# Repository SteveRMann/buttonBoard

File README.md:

# buttonBoard
Test board with four buttons, two LEDs and one PWM driver (200mA).

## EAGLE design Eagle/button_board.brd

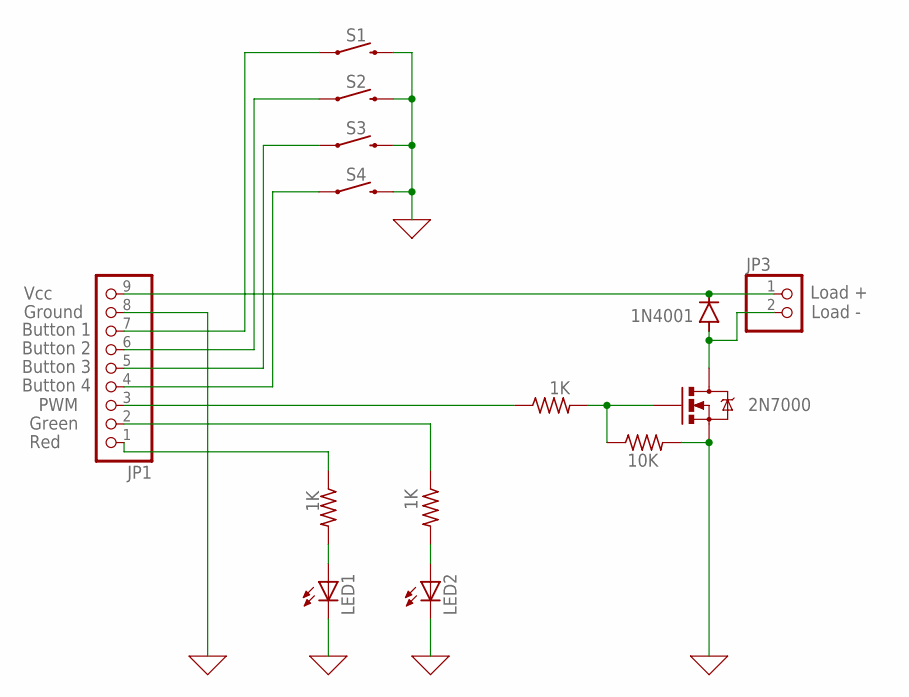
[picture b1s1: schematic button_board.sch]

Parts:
D1: 1N4001; DO-41
JP1: PINHD-1X9; 1X09
JP3: PINHD-1X2; 1X02
LED1, LED2: LED5MM
Q1: MOSFET-NCHANNEL2N7000; TO-92
R1, R3, R4: 1K; 0207/10
R2: 10K; 0207/10
S1, S2, S3, S4: MOMENTARY-SWITCH-SPST-PTH-6.0MM; TACTILE_SWITCH_PTH_6.0MM

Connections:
0: JP1.8, LED1.K (C), LED2.K (C), Q1.1 (S), R2.2, S1.3 (2), S2.3 (2), S3.3 (2), S4.3 (2)
unnamed: JP1.3, R1.1
unnamed: Q1.2 (G), R1.2, R2.1
unnamed: D1.A, JP3.2, Q1.3 (D)
unnamed: JP1.7, S1.1
unnamed: JP1.6, S2.1
unnamed: JP1.5, S3.1
unnamed: JP1.4, S4.1
unnamed: JP1.1, R3.1
unnamed: JP1.2, R4.1
unnamed: LED2.A, R4.2
unnamed: LED1.A, R3.2
unnamed: D1.C, JP1.9, JP3.1

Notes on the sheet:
Load +
Load -
Ground
2N7000
Green
Button 1
Button 2
Button 3
Button 4
PWM
Red
Vcc

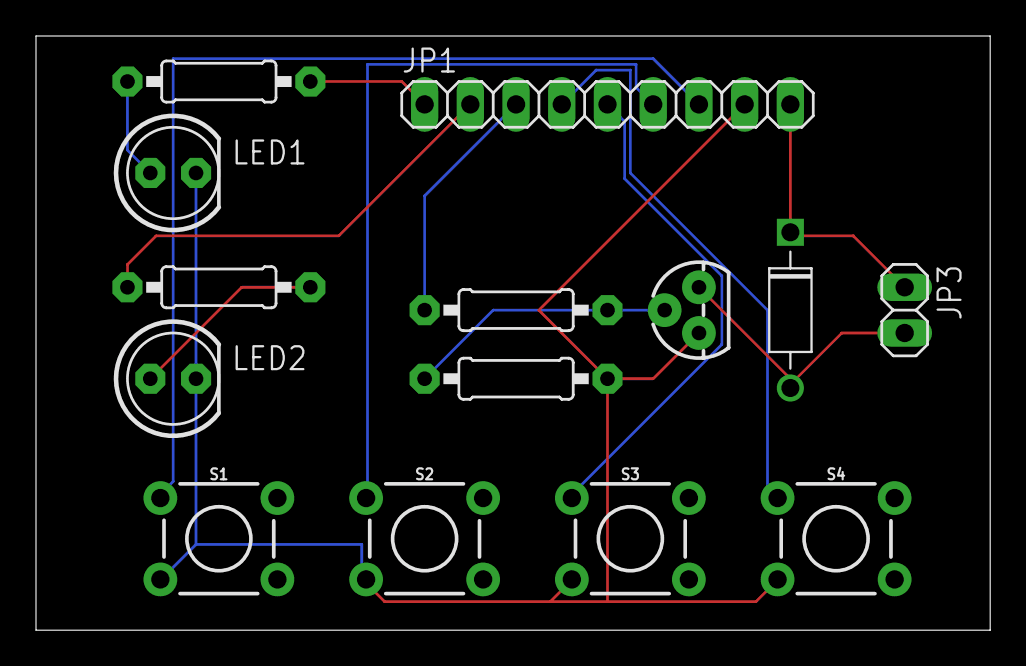
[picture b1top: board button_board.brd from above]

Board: 2 copper layers, 53.0 x 33.0 mm, 14 parts (0 on the bottom side), 13 nets.

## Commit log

2023-06-16 Added Eagle schematic and board files

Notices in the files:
parts and their libraries:
SparkFun-Switches: Licensing: Creative Commons ShareAlike 4.0 International - https://creativecommons.org/licenses/by-sa/4.0
